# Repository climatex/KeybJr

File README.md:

# KeybJr
Use any PS/2, AT or XT keyboard with the IBM PCjr, over the infrared or cable.

# More information
Check out my [website article](http://boginjr.com/it/hw/keybjr) to learn more!

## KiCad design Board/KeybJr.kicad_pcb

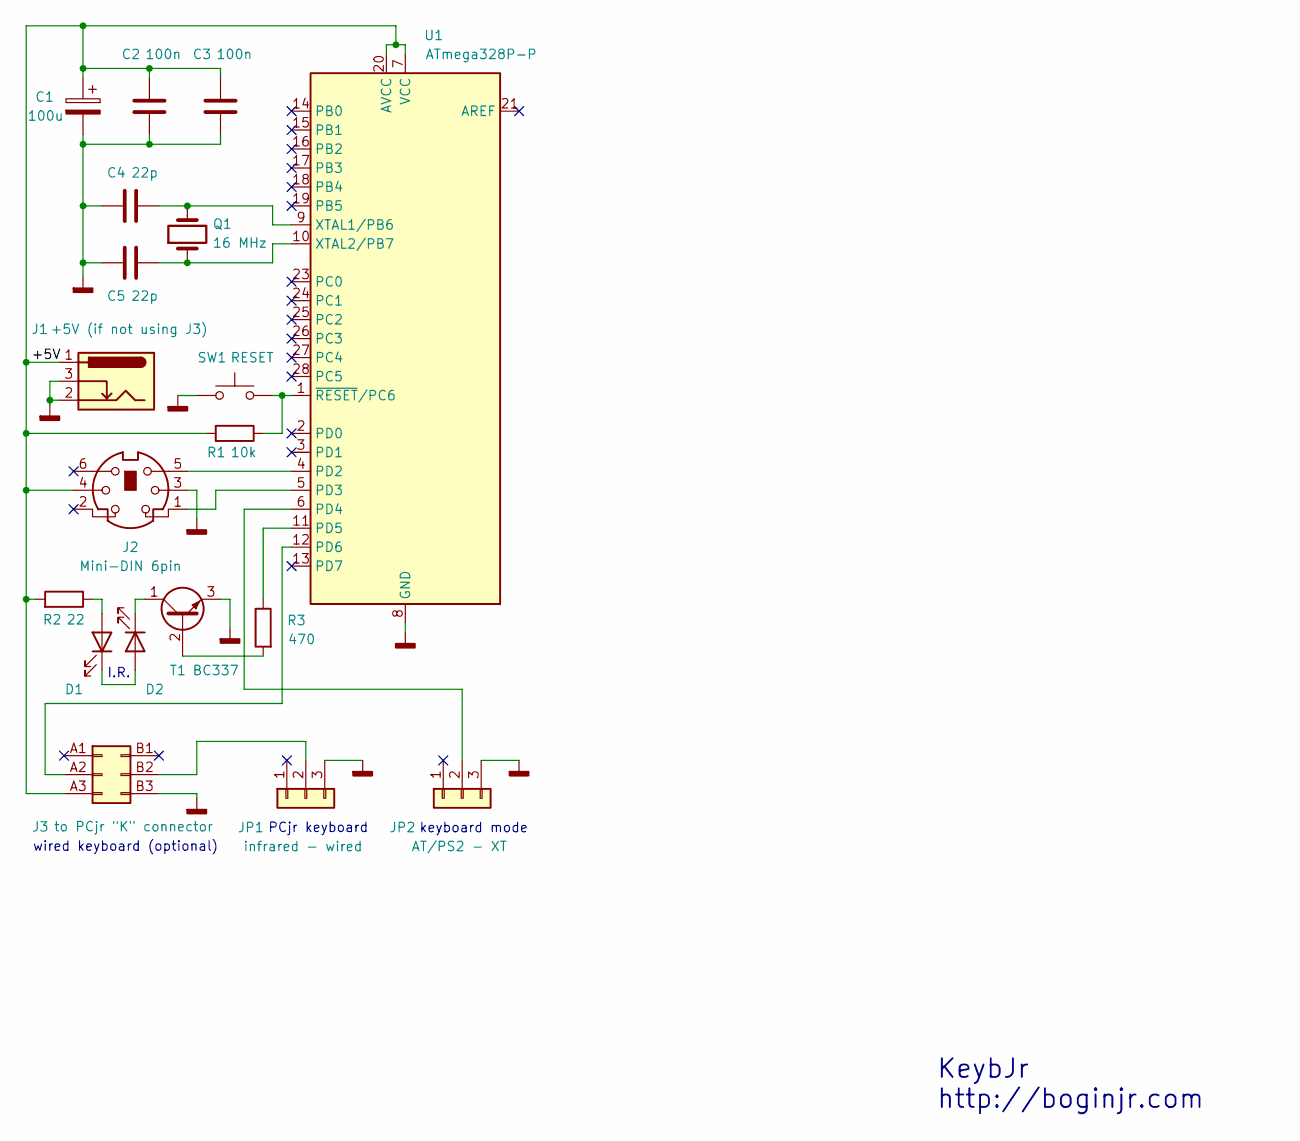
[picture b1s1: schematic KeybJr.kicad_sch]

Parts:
C1: 100u; CP_Radial_D6.3mm_P2.50mm
C2, C3: 100n; C_Disc_D7.5mm_W2.5mm_P5.00mm
C4, C5: 22p; C_Disc_D7.5mm_W2.5mm_P5.00mm
D1, D2: LED; LED_D5.0mm_IRGrey
J1: +5V (if not using J3); BarrelJack_Horizontal
J2: Mini-DIN 6pin; Mini_DIN6_Female_THT
J3: to PCjr "K" connector; PinHeader_2x03_P2.54mm_Vertical
JP1: infrared - wired; PinHeader_1x03_P2.54mm_Vertical
JP2: AT/PS2 - XT; PinHeader_1x03_P2.54mm_Vertical
Q1: 16 MHz; Crystal_HC49-U_Vertical
R1: 10k; R_Axial_DIN0207_L6.3mm_D2.5mm_P10.16mm_Horizontal
R2: 22; R_Axial_DIN0207_L6.3mm_D2.5mm_P10.16mm_Horizontal
R3: 470; R_Axial_DIN0207_L6.3mm_D2.5mm_P10.16mm_Horizontal
SW1: RESET; SW_PUSH_6mm
T1: BC337; TO-92_Inline
U1: ATmega328P-P; DIP-28_W7.62mm

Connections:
/+5V: C1.1, C2.1, C3.1, J1.1, J2.4, J3.A3 (Pin_a3), R1.2, R2.2, U1.7 (VCC), U1.20 (AVCC)
GNDD: C1.2, C2.2, C3.2, C4.1, C5.1, J1.2, J1.3, J2.3, J2.SH1, J2.SH2, J2.SH3, J3.B3 (Pin_b3), JP1.3, JP2.3, SW1.2, T1.3 (E), U1.8 (GND), U1.22 (GND)
unnamed: D1.2 (A), R2.1
unnamed: D1.1 (K), D2.2 (A)
unnamed: D2.1 (K), T1.1 (C)
unnamed: J3.A2 (Pin_a2), U1.12 (PD6)
unnamed: J3.B2 (Pin_b2), JP1.2
unnamed: JP2.2, U1.6 (PD4)
unnamed: R3.2, T1.2 (B)
unnamed: J2.5, U1.4 (PD2)
unnamed: J2.1, U1.5 (PD3)
unnamed: R3.1, U1.11 (PD5)
unnamed: C4.2, Q1.2, U1.9 (XTAL1/PB6)
unnamed: C5.2, Q1.1, U1.10 (XTAL2/PB7)
unnamed: R1.1, SW1.1, U1.1 (~RESET/PC6)

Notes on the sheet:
wired keyboard (optional)
KeybJr http://boginjr.com
keyboard mode
PCjr keyboard
I.R.

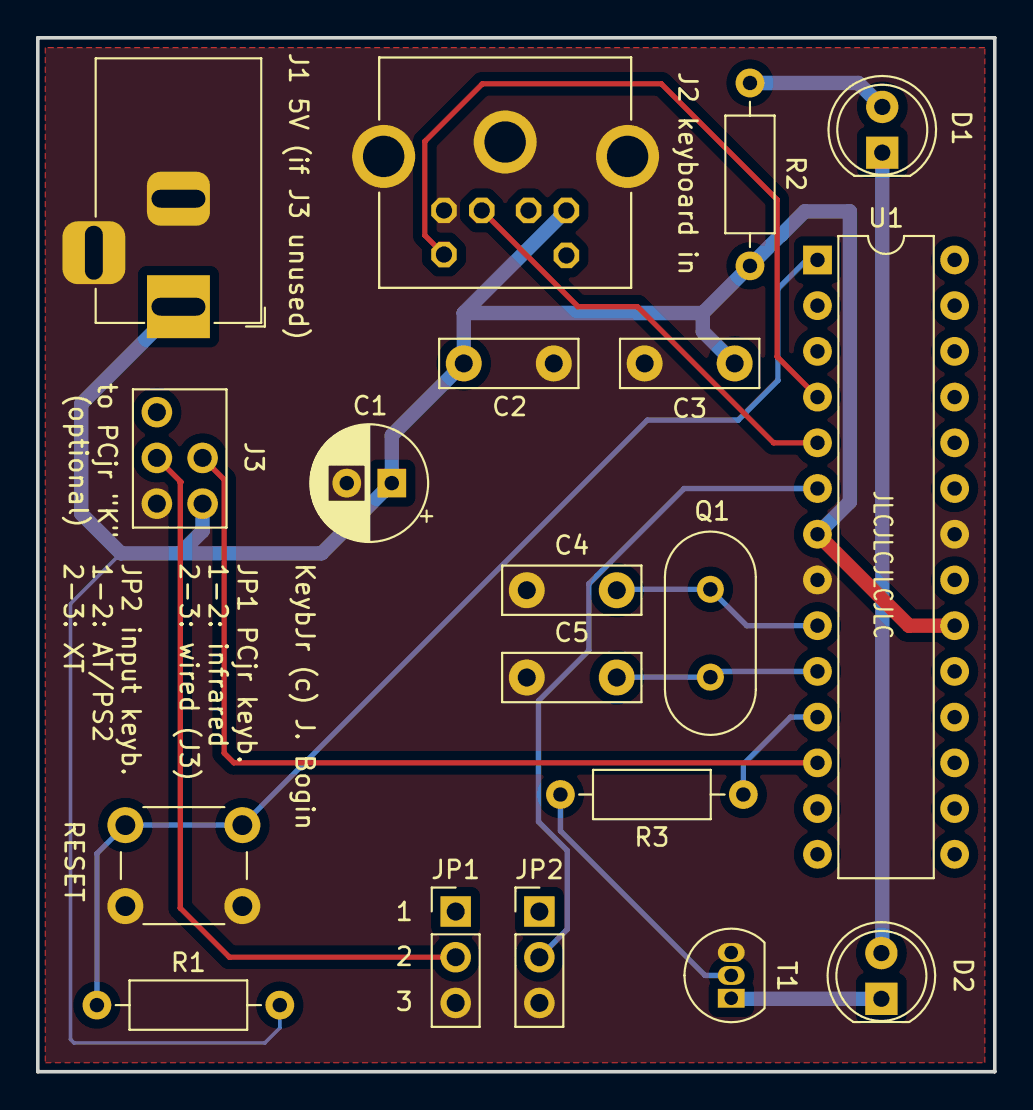
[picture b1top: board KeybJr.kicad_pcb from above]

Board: 2 copper layers, 53.2 x 57.4 mm, 19 parts (0 on the bottom side), 15 nets.

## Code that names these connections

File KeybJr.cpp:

/* Pin assignments as follows:
   PD2 (DIP ATmega328 pin 4)  - Keyboard clock input
   PD3 (    -||-      pin 5)  - Keyboard data input
   PD4 (    -||-      pin 6)  - Keyboard select (AT/XT) input
   PD5 (    -||-      pin 11) - PCjr infrared output
   PD6 (    -||-      pin 12) - PCjr cable output
   PD7 (    -||-      pin 13) - optional XT /RESET line handling
 */

#include <Arduino.h>
#include "IR.h"
#include "KeybXtAt.h"
#include "KeybPcJr.h"

// Global variable - using AT or XT keyboard depending on jumper
uint8_t usingXtKeyboard = 0;

void setup()
{  
  // Normal behavior: PD5 + PD6 + PD7 outputs, PD4 + PD3 + PD2 as inputs
  DDRD = 0xe2;
  
  // By default, /RESET, keybselect, keybclock and Jr cable output pulled up...
  PORTD |= 0xD4;
  // .. and the infrared pulled down
  PORTD &= 0xDF;
  _delay_ms(10);
  
  // If using XT keyboard - PD4 jumpered to GND
  usingXtKeyboard = !((PIND >> 4) & 1);
  
  // Initialize chosen keyboard  
  InitializeKeyboard();
}

void loop()
{
  // Get a scancode from the keyboard and convert it to XT (if on AT/PS2 keyboard).  
  // Then convert it for PCjr finesse and transmit through infrared and cable.
  // During TX, the keyboard waits.
  
  while(1)
  {
    const uint8_t scanCode = ReadKeyboard();
    DisableKeyboard();
    SendScancode(scanCode);
    EnableKeyboard(); 
  }
}

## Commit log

2022-03-21 Code push
2022-04-07 Implement XT keyboard reset
2024-10-25 Add board PCB, bugfixes
2025-06-11 Improve PS/2 reset routine
